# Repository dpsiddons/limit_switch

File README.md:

# limit_switch
A simple and compact way to add motion limits to a mechanism. It uses a small magnet and a hall-effect switch IC mounted on a small PCB.
It was designed in particular for the Openflexure_Microscope project, and the file limit_Switches.odt describes how the first implementation was done. (https://gitlab.com/openflexure/openflexure-microscope).

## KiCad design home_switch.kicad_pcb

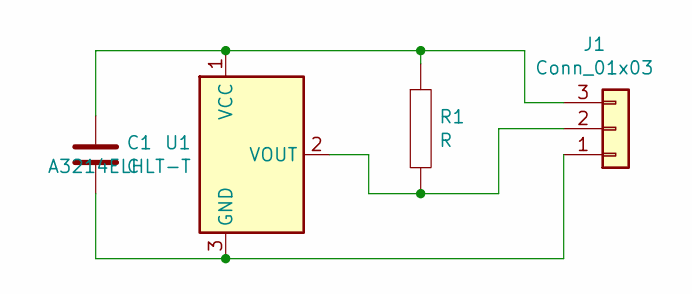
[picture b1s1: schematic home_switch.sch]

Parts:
C1: C; C_0603_1608Metric
J1: Conn_01x03; PinHeader_1x03_P1.00mm_Horizontal
R1: R; R_0603_1608Metric
U1: A3214ELHLT-T; SOT-23

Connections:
unnamed: C1.1, J1.3, R1.1, U1.1 (VCC)
unnamed: C1.2, J1.1, U1.3 (GND)
unnamed: J1.2, R1.2, U1.2 (VOUT)

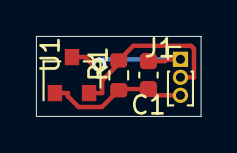
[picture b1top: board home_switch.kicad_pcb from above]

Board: 2 copper layers, 9.1 x 4.4 mm, 4 parts (0 on the bottom side), 3 nets.
